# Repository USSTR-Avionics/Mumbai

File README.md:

`aamchi mumbai!!!`

# Introduction

Welcome to our hardware-based repository, dedicated to providing innovative designs for modular boards that utilize the CANbus interface. At our repository, we strive to bring the benefits of modularity to hardware design, allowing for greater flexibility, scalability, and customization. Our designs are built using the robust and reliable CANbus interface, ensuring efficient communication and seamless integration between modules. Whether you're a hardware enthusiast, a researcher, or an engineer looking to build custom hardware solutions, our repository has something to offer. Our goal is to create a community of like-minded individuals who are passionate about hardware design, and we invite you to join us on this exciting journey. Browse our collection of designs, collaborate with others, and let's push the boundaries of what's possible with modular hardware.

PDB and GPS copied over from: https://github.com/USSTR-Avionics/PDB and https://github.com/USSTR-Avionics/gps-board

RF board based on OpenLST: https://github.com/OpenLST/openlst-hw

## Standard and Unified Connector Kit
Pinout  
10x2 connector

|  | 1 | 2 | 3 | 4 | 5 | 6 | 7 | 8 | 9 | 10 |
|---|---|---|---|---|---|---|---|---|---|---|
| **A** | GND | 3V3 |GND | 3V3 | GND | 5V | GND | 5V | GND | Bus voltage | 
| **B** | GND | CAN high | CAN low | GND | GPIO | GPIO | GPIO | GPIO | GPIO  | GPIO  

(left to right, topview)

[hard to flip header](https://www.digikey.ca/en/products/detail/sullins-connector-solutions/SFH11-PBPC-D10-ST-BK/1990090)

## PCB Dimensions Drawing

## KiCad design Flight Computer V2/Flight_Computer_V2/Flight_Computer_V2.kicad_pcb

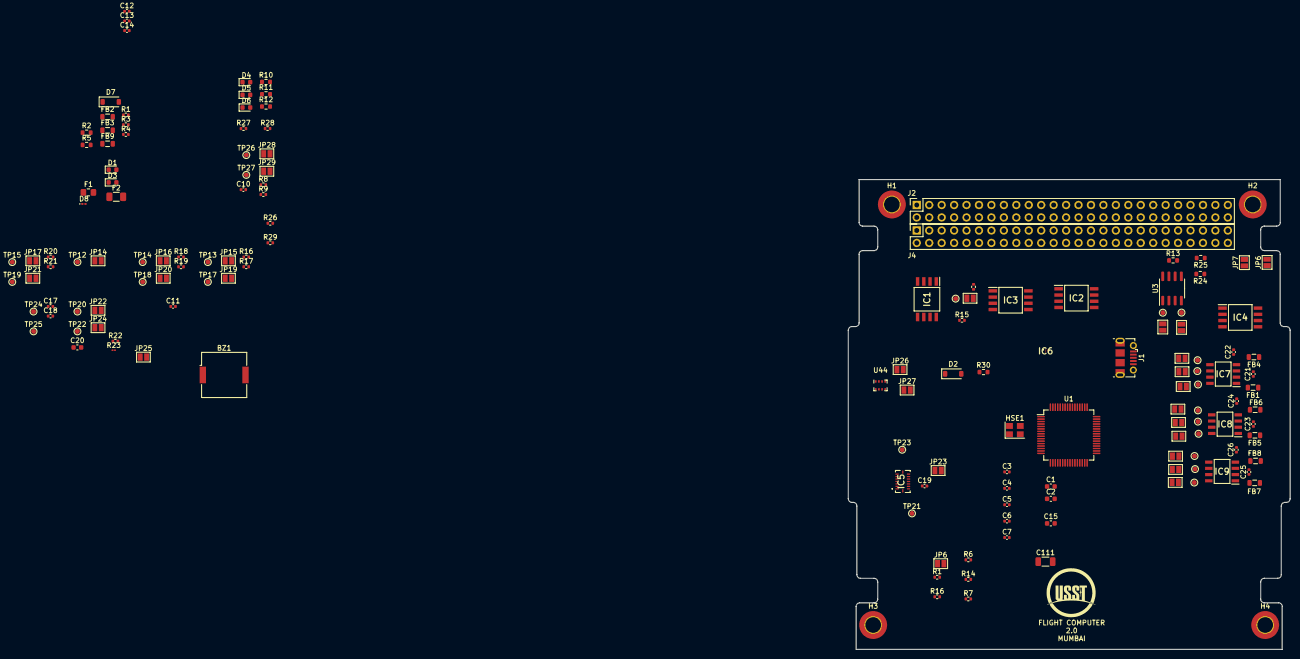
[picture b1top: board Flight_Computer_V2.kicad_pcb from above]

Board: 4 copper layers, 90.2 x 95.9 mm, 154 parts (0 on the bottom side), 82 nets, no tracks yet.

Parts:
BZ1: Active_Buzzer; Buzzer_Murata_PKMCS0909E
C1, C2: 2.2uF; C_0603_1608Metric
C3, C4, C5, C6, C7, C11, C14, C19: 100n; C_0402_1005Metric
C10, C22, C24, C26: 0.1u; C_0402_1005Metric
C12, C13: 10p; C_0402_1005Metric
C15: 10n; C_0603_1608Metric
C17, C18: 100nF; C_0402_1005Metric
C20: 2.2u; C_0603_1608Metric
C21, C23, C25: 1p; C_0402_1005Metric
C111: 4u7; C_1206_3216Metric
D1, D6: RED; LED_0603_1608Metric
D2, D7: B5819W; D_SOD-123
D3: Red; LED_0603_1608Metric
D4: GREEN; LED_0603_1608Metric
D5: YELLOW; LED_0603_1608Metric
D8: RED; LED_0201_0603Metric
F1: 500 mA; Fuse_0805_2012Metric_Pad1.15x1.40mm_HandSolder
F2: 500 mA; Fuse_1206_3216Metric
FB1, FB4, FB5, FB6, FB7, FB8: Ferrite; L_0805_2012Metric
FB2, FB9: 600 @ 600 MHz; L_0805_2012Metric
FB3: 100 @ 100 MHz; L_0805_2012Metric
H1, H2, H3, H4: MountingHole_Pad; MountingHole_3.2mm_M3_ISO7380_Pad_TopBottom
HSE1: 16MHz; Crystal_SMD_3225-4Pin_3.2x2.5mm
IC1, IC2, IC3, IC4: MB85RC256VPF-G-JNERE2; SOIC127P798X210-8N
IC5: BMI088
IC6: MMC5603NJ
IC7, IC8, IC9: MAX31855KASA+T; SOIC127P600X175-8N
J1: USB_B_Micro; USB_Micro-B_Molex-105017-0001
J2, J4: Conn_02x26_Odd_Even; PinSocket_2x26_P2.54mm_Vertical
JP1, JP2, JP3, JP4, JP5, JP6, JP6#2, JP7, JP8, JP9, JP10, JP11, JP12, JP13, JP14, JP15, JP16, JP17, JP18, JP19, JP20, JP21, JP22, JP23, JP24, JP25, JP26, JP27, JP28, JP29: SolderJumper-2_P1.3mm_Open_Pad1.0x1.5mm
R1, R1#2, R6, R7, R14, R14#2, R15, R16, R16#2, R17, R18, R19, R20, R21: 10k; R_0402_1005Metric
R2, R30: 1.5k; R_0603_1608Metric
R3, R4: 1.5k; R_0402_1005Metric
R5: 2.2k; R_0603_1608Metric
R8, R9: 4.7k; R_0402_1005Metric
R10, R11, R12: 500; R_0603_1608Metric
R13: 120; R_0603_1608Metric
R22: 2.7k; R_0402_1005Metric
R23: 2.7k; R_01005_0402Metric
R24, R25: 2k; R_0603_1608Metric
R26, R27, R28, R29: 150; R_0402_1005Metric
TP1, TP2, TP3, TP4, TP5, TP6, TP7, TP8, TP9, TP10, TP11, TP12, TP13, TP14, TP15, TP16, TP17, TP18, TP19, TP20, TP21, TP22, TP23, TP24, TP25, TP26, TP27: TestPoint_Small; TestPoint_Pad_D1.0mm
U1: STM32F405RGTx; LQFP-64_10x10mm_P0.5mm
U3: MCP2562-E-SN; SOIC-8_3.9x4.9mm_P1.27mm
U44: BMP280; Bosch_LGA-8_2x2.5mm_P0.65mm_ClockwisePinNumbering

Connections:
3V3IN: D2.2 (A), J4.27, J4.28
5VIN: D7.2 (A), J2.47, J2.49, J4.25, J4.26
+3.3V: C10.1, C17.1, C18.1, D1.2 (A), FB2.2, JP6.1 (A), R3.1, R4.1, R8.2, R9.2, R24.1, R25.1, U3.5 (Vio), U44.2 (CSB), U44.6 (VDDIO), U44.8 (VDD)
+3.3VA: C14.1, C15.1, FB3.2, U1.13 (VDDA)
+3V3: C3.1, C4.1, C5.1, C6.1, C7.1, C11.1, C19.1, C20.1, C22.1, C24.1, C26.1, C111.1, FB3.1, IC1.8 (VDD), IC2.1 (A0), IC2.8 (VDD), IC3.2 (A1), IC3.8 (VDD), IC4.3 (A2), IC4.8 (VDD), IC5.3 (VDD), IC5.7 (PS), IC5.11 (VDDIO), IC6.B1 (VDD), IC7.4 (VCC), IC8.4 (VCC), IC9.4 (VCC), R6.1, R7.1, R14.1, R14#2.1, R15.1, R16.1, R16#2.1, R17.1, R18.1, R19.1, R20.1, R21.1, R22.1, R23.1, U1.1 (VBAT), U1.19 (VDD), U1.32 (VDD), U1.48 (VDD), U1.64 (VDD)
+5V: D8.2 (A), FB9.2, U3.3 (VDD)
/420_1: R26.2, U1.14 (PA0)
/420_2: R27.2, U1.15 (PA1)
/420_3: R28.2, U1.16 (PA2)
/420_4: R29.2, U1.17 (PA3)
/ACCELROMETER/SCL: J2.43, JP7.1 (A), JP18.2 (B), JP19.2 (B), JP20.2 (B), JP21.2 (B), JP24.2 (B), JP25.2 (B), JP27.2 (B), JP28.2 (B), R3.2, R14#2.2, R16.2, R18.2, R20.2, R25.2, U1.58 (PB6)
/ACCELROMETER/SDA: J2.41, JP6#2.1 (A), JP14.2 (B), JP15.2 (B), JP16.2 (B), JP17.2 (B), JP22.2 (B), JP23.2 (B), JP26.2 (B), JP29.1 (A), R4.2, R24.2, U1.59 (PB7)
/BUZZER: BZ1.1 (-), U1.41 (PA8)
/CAN CONTROLLER/CANH: J2.42, R13.1, U3.7 (CANH)
/CAN CONTROLLER/CANL: J2.44, R13.2, U3.6 (CANL)
/CAN CONTROLLER/CAN_RX: JP5.2 (B), U1.61 (PB8)
/CAN CONTROLLER/CAN_TX: JP4.2 (B), U1.62 (PB9)
/GREEN: R10.1, U1.20 (PA4)
/MICROCONTROLLER/BOOT0: JP6.2 (B), R1.2, R1#2.2, U1.60 (BOOT0)
/MICROCONTROLLER/HSC_IN: C12.1, HSE1.1, U1.5 (PH0)
/MICROCONTROLLER/HSC_OUT: C13.1, HSE1.3, U1.6 (PH1)
/MICROCONTROLLER/PWR_LED_K: D1.1 (K), D8.1 (K), R2.1, R30.1
/MICROCONTROLLER/SPI1_CLK: JP3.2 (B), JP10.2 (B), JP13.2 (B), U1.21 (PA5)
/MICROCONTROLLER/SPI1_MISO: JP1.2 (B), JP8.2 (B), JP11.2 (B), U1.22 (PA6)
/MICROCONTROLLER/USB_D+: J1.3 (D+), U1.45 (PA12)
/MICROCONTROLLER/USB_D-: J1.2 (D-), U1.44 (PA11)
/MICROCONTROLLER/VCAP1: C1.1, U1.31 (VCAP_1)
/MICROCONTROLLER/VCAP2: C2.1, U1.47 (VCAP_2)
/RED: R12.1, U1.27 (PB1)
/TCSS1: JP2.2 (B), U1.8 (PC0)
/TCSS2: JP9.2 (B), U1.9 (PC1)
/TCSS3: JP12.2 (B), U1.10 (PC2)
/WP1: IC1.7 (WP), U1.11 (PC3)
/WP2: IC2.7 (WP), U1.24 (PC4)
/WP3: IC3.7 (WP), U1.25 (PC5)
/WP4: IC4.7 (WP), U1.37 (PC6)
/YELLOW: R11.1, U1.26 (PB0)
GND: BZ1.2 (+), C1.2, C2.2, C10.2, C11.2, C12.2, C13.2, C14.2, C15.2, C17.2, C18.2, C19.2, C20.2, C22.2, C24.2, C26.2, D4.1 (K), D5.1 (K), D6.1 (K), H1.1, H2.1, H3.1, H4.1, HSE1.2, HSE1.4, IC1.4 (VSS), IC2.4 (VSS), IC3.4 (VSS), IC4.4 (VSS), IC5.4 (GNDA), IC5.6 (GNDIO), IC5.10 (SDO2), IC5.15 (SDO1), IC6.A1 (VSA), IC7.1 (GND), IC8.1 (GND), IC9.1 (GND), J1.5 (GND), J4.9, J4.14, J4.17, J4.29, J4.30, J4.32, J4.48, J4.49, R1#2.1, R2.2, R5.2, R26.1, R27.1, R28.1, R29.1, R30.2, U1.12 (VSSA), U1.18 (VSS), U1.63 (VSS), U3.2 (VSS), U3.8 (STBY), U44.1 (GND), U44.5 (SDO), U44.7 (GND)
unnamed: C3.2, C4.2, C5.2, C6.2, C7.2, C111.2
unnamed: D2.1 (K), F1.1
unnamed: D3.2 (A), U1.33 (PB12)
unnamed: D3.1 (K), R5.1
unnamed: D4.2 (A), R10.2
unnamed: D5.2 (A), R11.2
unnamed: D6.2 (A), R12.2
unnamed: D7.1 (K), F2.1
unnamed: F1.2, FB2.1
unnamed: F2.2, FB9.1
unnamed: IC1.6 (SCL), JP18.1 (A), R6.2, TP16.1
unnamed: IC1.5 (SDA), JP14.1 (A), R15.2, TP12.1
unnamed: IC2.6 (SCL), JP19.1 (A), R7.2, TP17.1
unnamed: IC2.5 (SDA), JP15.1 (A), R17.2, TP13.1
unnamed: IC3.6 (SCL), JP20.1 (A), R14.2, TP18.1
unnamed: IC3.5 (SDA), JP16.1 (A), R19.2, TP14.1
unnamed: IC4.6 (SCL), JP21.1 (A), R16#2.2, TP19.1
unnamed: IC4.5 (SDA), JP17.1 (A), R21.2, TP15.1
unnamed: IC5.8 (SCL/SCK), JP25.1 (A), TP23.1
unnamed: IC5.9 (SDA/SDI), JP23.1 (A), TP21.1
unnamed: IC6.A2 (SCL), JP24.1 (A), R22.2, TP22.1
unnamed: IC6.B2 (SDA), JP22.1 (A), R23.2, TP20.1
unnamed: IC7.5 (SCK), JP3.1 (A), TP3.1
unnamed: IC7.7 (SO), JP1.1 (A), TP1.1
unnamed: C21.2, FB4.2, IC7.3 (T+)
unnamed: C21.1, FB1.2, IC7.2 (T-)
unnamed: IC7.6 (~CS), JP2.1 (A), TP2.1
unnamed: IC8.5 (SCK), JP10.1 (A), TP8.1
unnamed: IC8.7 (SO), JP8.1 (A), TP6.1
unnamed: C23.2, FB6.2, IC8.3 (T+)
unnamed: C23.1, FB5.2, IC8.2 (T-)
unnamed: IC8.6 (~CS), JP9.1 (A), TP7.1
unnamed: IC9.5 (SCK), JP13.1 (A), TP11.1
unnamed: IC9.7 (SO), JP11.1 (A), TP9.1
unnamed: C25.2, FB8.2, IC9.3 (T+)
unnamed: C25.1, FB7.2, IC9.2 (T-)
unnamed: IC9.6 (~CS), JP12.1 (A), TP10.1
unnamed: JP4.1 (A), TP4.1, U3.1 (TXD)
unnamed: JP5.1 (A), TP5.1, U3.4 (RXD)
unnamed: JP26.1 (A), TP24.1, U44.3 (SDI)
unnamed: JP27.1 (A), TP25.1, U44.4 (SCK)
unnamed: JP28.1 (A), TP26.1
unnamed: JP29.2 (B), TP27.1
VBUS: J1.1 (VBUS), J4.35, J4.36

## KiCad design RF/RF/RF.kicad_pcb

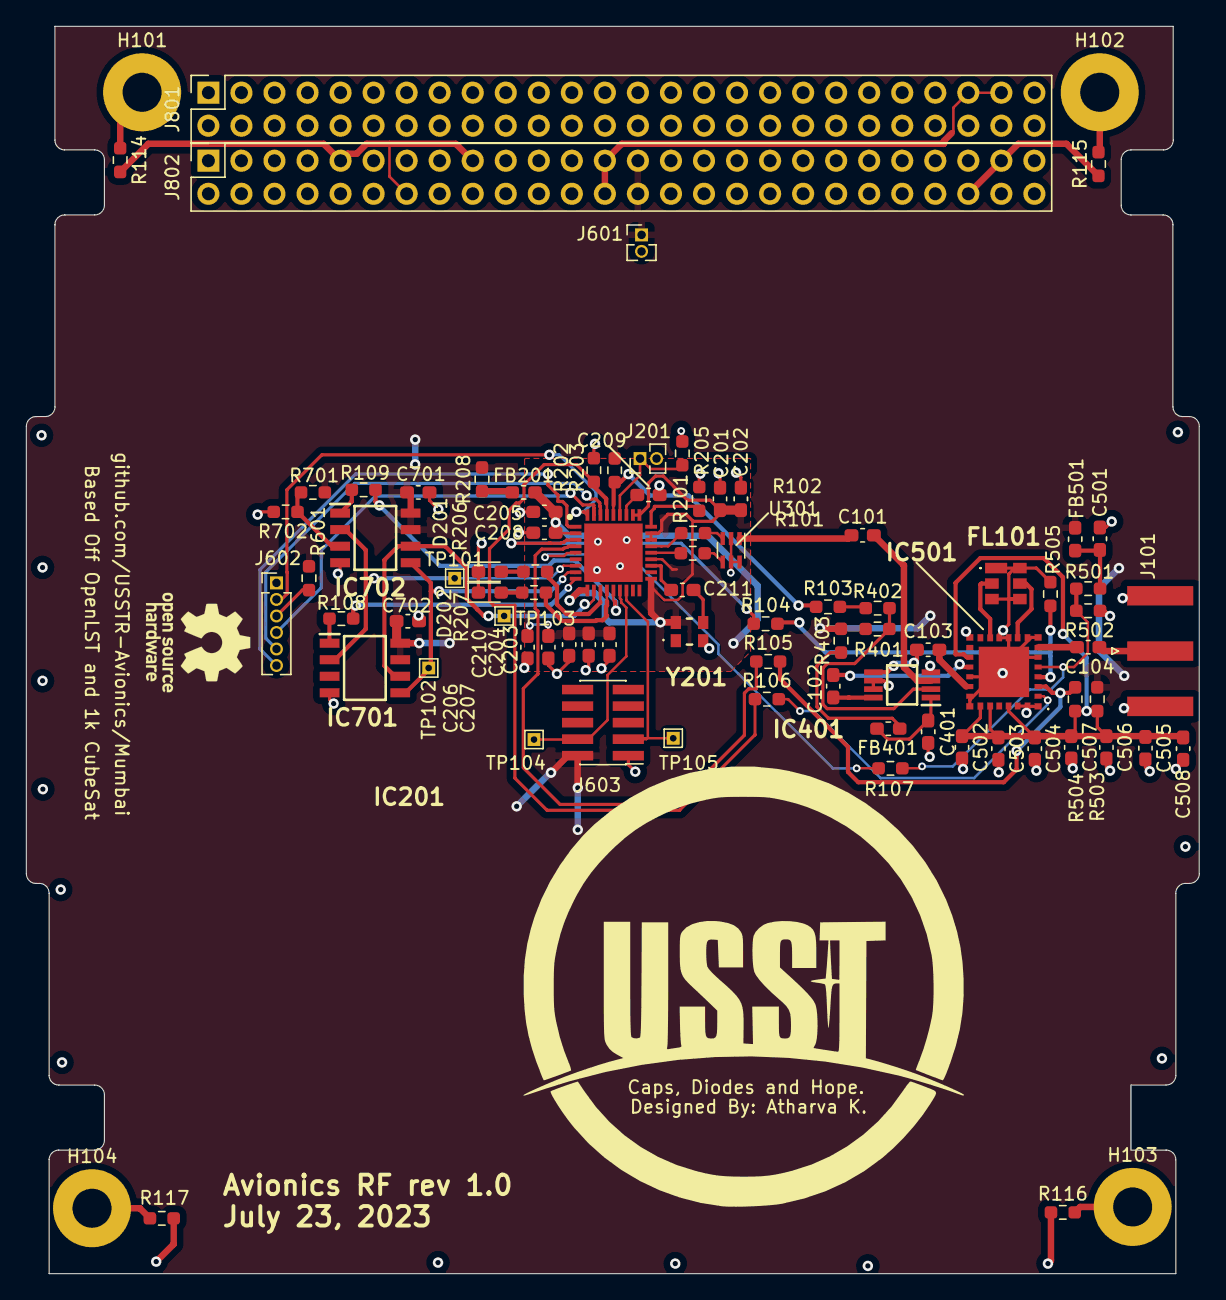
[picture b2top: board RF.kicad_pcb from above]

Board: 4 copper layers, 90.2 x 95.9 mm, 86 parts (0 on the bottom side), 62 nets.

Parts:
C101, C102, C103, C104, C207, C208: 220pF; C_0603_1608Metric_Pad1.08x0.95mm_HandSolder
C201, C202, C209, C507: 1uF; C_0603_1608Metric_Pad1.08x0.95mm_HandSolder
C203, C204, C205, C206, C210, C401, C501, C505, C506, C508, C701, C702: 0.1uF; C_0603_1608Metric_Pad1.08x0.95mm_HandSolder
C211: 0.01uF; C_0603_1608Metric_Pad1.08x0.95mm_HandSolder
C502, C503: 47uF; C_0603_1608Metric_Pad1.08x0.95mm_HandSolder
C504: 4.7uF; C_0603_1608Metric_Pad1.08x0.95mm_HandSolder
D201, D202: LED; LED_0603_1608Metric_Pad1.05x0.95mm_HandSolder
FB201: Z = 1k@ 100MHz; L_0603_1608Metric_Pad1.05x0.95mm_HandSolder
FB401, FB501: Z = 1k @ 100M; L_0603_1608Metric_Pad1.05x0.95mm_HandSolder
FL101: SF2446E
H101, H102, H103, H104: MountingHole_Pad; MountingHole_3mm_Pad
IC201: CC1110F16RHHR; QFN50P600X600X100-37N-D
IC401: PE4250MLI-Z; SOP65P488X107-8N
IC501: RFFM6406SR; RFFM6403
IC701: 23K256-I_SN; SOIC127P600X175-8N
IC702: SST25VF512A-33-4C-SAE; SOIC127P600X175-8N
J101: Conn_Coaxial; SMA_Amphenol_132289_EdgeMount
J201, J601: Conn_01x02; PinHeader_1x02_P1.27mm_Vertical
J602: Conn_01x06; PinHeader_1x06_P1.27mm_Vertical
J603: Conn_02x05_Odd_Even; PinHeader_2x05_P1.27mm_Vertical_SMD
J801, J802: Conn_02x26_Odd_Even; PinSocket_2x26_P2.54mm_Vertical
R101, R102, R103, R104, R105, R106, R107, R108, R109, R208, R402, R403, R503: 0R; R_0603_1608Metric_Pad0.98x0.95mm_HandSolder
R114, R115, R116, R117, R401, R601, R701: DNP; R_0603_1608Metric_Pad0.98x0.95mm_HandSolder
R201: 56k 1%; R_0603_1608Metric_Pad0.98x0.95mm_HandSolder
R202, R203: 10k 1%; R_0603_1608Metric_Pad0.98x0.95mm_HandSolder
R205, R702: 10k; R_0603_1608Metric_Pad0.98x0.95mm_HandSolder
R206, R207, R504, R505: 1k; R_0603_1608Metric_Pad0.98x0.95mm_HandSolder
R501: 3.09k 1%; R_0603_1608Metric_Pad0.98x0.95mm_HandSolder
R502: 6.65k 1%; R_0603_1608Metric_Pad0.98x0.95mm_HandSolder
TP101: MISO; TestPoint_THTPad_1.0x1.0mm_Drill0.5mm
TP102: MOSI; TestPoint_THTPad_1.0x1.0mm_Drill0.5mm
TP103: SCK; TestPoint_THTPad_1.0x1.0mm_Drill0.5mm
TP104: CC_DD; TestPoint_THTPad_1.0x1.0mm_Drill0.5mm
TP105: CC_DC; TestPoint_THTPad_1.0x1.0mm_Drill0.5mm
U301: 0433BM15A0001; Balun_Johanson_0896BM15A0001
Y201: TG2520SMN 27.000M-MCGNNM3; TG2520SMN25000MMCGNNM3

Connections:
+3.3V: C701.1, C702.1, FB501.2, IC701.7 (~HOLD), IC701.8 (VCC), IC702.7 (HOLD#), IC702.8 (VDD), J601.1, J603.2, J802.27, J802.28, R203.1, R208.2, R401.1, R403.2, R503.2, R601.2, R701.1
+3.3VA: C201.1, C202.1, C203.1, C204.1, C205.1, C206.1, C207.1, C208.1, C210.1, FB201.2, IC201.2 (DVDD_1), IC201.10 (DVDD_2), IC201.19 (AVDD_1), IC201.22 (AVDD_2), IC201.25 (AVDD_3), IC201.26 (AVDD_4), IC201.28 (GUARD), IC201.29 (AVDD_DREG), J201.2, Y201.4 (VCC)
+5V: J801.47, J801.49, J802.25, J802.26
/Balun/CC_RF_N: R102.2, U301.3
/Balun/CC_RF_P: R101.2, U301.4
/Balun/UNBALANCED_RF: C101.1, U301.1
/CC1110/AIN0: IC201.5 (P0_0), R107.1
/CC1110/CC_DC: IC201.16 (P2_2), J603.3, TP105.1
/CC1110/CC_DD: IC201.15 (P2_1), J603.4, TP104.1
/CC1110/CC_RF_N: IC201.24 (RF_N), R102.1
/CC1110/CC_RF_P: IC201.23 (RF_P), R101.1
/CC1110/CC_SOC_OC: C211.2, IC201.21 (XOSC_Q1)
/CC1110/LST_TX_MODE: IC201.33 (P1_6), R106.1, R202.1
/CC1110/RF_BYP: IC201.3 (P1_1), R104.1
/CC1110/RF_EN: IC201.4 (P1_0), R105.1
/CC1110/UART0_CTS: IC201.1 (P1_2), J602.6
/CC1110/UART0_RTS: IC201.36 (P1_3), J602.2
/CC1110/UART0_RX: IC201.35 (P1_4), J602.4
/CC1110/UART0_TX: IC201.34 (P1_5), J602.5
/CC1110/~FLASH_CS: IC201.14 (P2_0), R109.1
/CC1110/~LST_RX_MODE: IC201.32 (P1_7), R103.1, R203.2
/CC1110/~SRAM_CS: IC201.9 (P0_4), R108.1
/External Memory/~FLASH_CS: IC702.1 (CE#), R109.2
/External Memory/~SRAM_CS: IC701.1 (~CS), R108.2
/MISO: IC201.7 (P0_2), IC701.2 (SO), IC702.2 (SO), TP101.1
/MOSI: IC201.8 (P0_3), IC701.5 (SI), IC702.5 (SI), TP102.1
/RF Front End/ANTENNA: C104.1, IC501.7 (ANT)
/RF Front End/LST_TX_MODE: IC501.2 (TR), R106.2
/RF Front End/PA_VAPC: IC501.5 (VAPC), R107.2, R501.2, R502.1
/RF Front End/RF_BYP: IC501.4 (BYP), R104.2, R505.2
/RF Front End/RF_EN: IC501.3 (EN), R105.2, R504.1
/RF Front End/RX: C102.2, IC501.18 (RX)
/RF Front End/SAW1: FL101.5 (OUTPUT), IC501.10 (SAW1)
/RF Front End/SAW2: FL101.2 (INPUT), IC501.13 (SAW2)
/RF Front End/TX: C103.2, IC501.20 (TX)
/RF Switch/RX: C102.1, IC401.8 (RF2)
/RF Switch/TX: C103.1, IC401.5 (RF1)
/RF Switch/UNBALANCED_RF: C101.2, IC401.3 (RFC)
/RF Switch/~LST_RX_MODE: R103.2, R402.1
/SCK: IC201.11 (P0_5), IC701.6 (SCK), IC702.6 (SCK), TP103.1
GND: C201.2, C202.2, C203.2, C204.2, C205.2, C206.2, C207.2, C208.2, C209.2, C210.2, C401.2, C501.2, C502.2, C503.2, C504.2, C505.2, C506.2, C507.2, C508.2, C701.2, C702.2, D201.1 (K), D202.1 (K), FL101.1 (GND_1), FL101.3 (GND_2), FL101.4 (GND_3), FL101.6 (GND_4), IC201.37 (AGND), IC401.4 (N/C_OR_GND), IC401.6 (GND_1), IC401.7 (GND_2), IC501.1 (GND_1), IC501.6 (GND_2), IC501.8 (GND_3), IC501.9 (GND_4), IC501.11 (GND_5), IC501.12 (GND_6), IC501.15 (GND_7), IC501.19 (GND_8), IC501.21 (GND_9), IC501.22 (GND_10), IC501.27 (GND_11), IC501.28 (GND_12), IC501.29 (EP), IC701.4 (VSS), IC702.4 (VSS), J101.2 (Ext), J601.2, J602.1, J603.1, J802.9, J802.14, J802.17, J802.29, J802.30, J802.32, J802.48, J802.49, R114.1, R115.1, R116.1, R117.1, R201.2, R202.2, R205.2, R502.2, R505.1, R702.2, U301.2 (GND), U301.5 (GND), U301.6 (GND), Y201.2 (GND)
unnamed: C501.1, FB501.1, R501.1
unnamed: D201.2 (A), R206.2
unnamed: D202.2 (A), R207.2
unnamed: FB201.1, R208.1
unnamed: FB401.1, R403.1
unnamed: H101.1, R114.2
unnamed: H102.1, R115.2
unnamed: H103.1, R116.2
unnamed: H104.1, R117.2
unnamed: C209.1, IC201.30 (DCOUPL)
unnamed: IC201.12 (P0_6), R206.1
unnamed: IC201.13 (P0_7), R207.1
unnamed: IC201.27 (RBIAS), R201.1
unnamed: IC201.31 (RESET_N), J201.1, R205.1
unnamed: IC401.2 (V1), R401.2, R402.2
unnamed: C401.1, FB401.2, IC401.1 (V2)
unnamed: C502.1, C503.1, C504.1, C505.1, C506.1, C507.1, C508.1, IC501.17 (VCC_RX), IC501.23 (VDD), IC501.24 (VCC_TX1), IC501.26 (VCC_TX2), R503.1, R504.2
unnamed: IC702.3 (WP#), R701.2, R702.1
unnamed: C104.2, J101.1 (In)
unnamed: J602.3, R601.1
unnamed: C211.1, Y201.3 (OUT)

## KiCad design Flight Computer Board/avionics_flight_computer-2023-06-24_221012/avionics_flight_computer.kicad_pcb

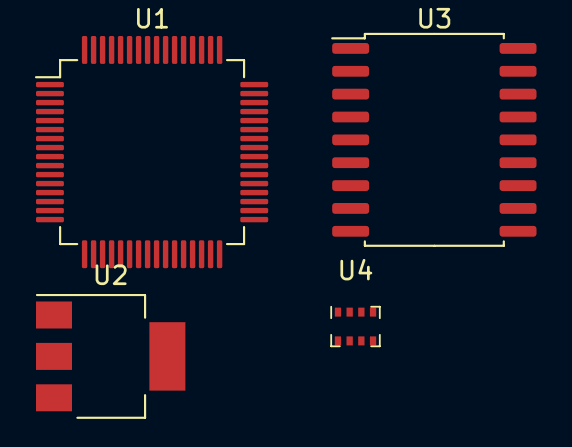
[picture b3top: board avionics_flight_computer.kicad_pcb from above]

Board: 2 copper layers, 4 parts (0 on the bottom side), 2 nets, no tracks yet.

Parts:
U1: STM32F405RGTx; LQFP-64_10x10mm_P0.5mm
U2: AMS1117-3.3; SOT-223-3_TabPin2
U3: MCP2515-xSO; SOIC-18W_7.5x11.6mm_P1.27mm
U4: BMP280; Bosch_LGA-8_2x2.5mm_P0.65mm_ClockwisePinNumbering

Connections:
3.3V: U1.1 (VBAT), U1.19 (VDD), U1.32 (VDD), U1.48 (VDD), U1.64 (VDD), U2.2 (VO), U4.2 (CSB), U4.6 (VDDIO), U4.8 (VDD)
GND: U1.12 (VSSA), U1.18 (VSS), U1.63 (VSS), U2.1 (GND), U3.9 (VSS), U4.1 (GND), U4.5 (SDO), U4.7 (GND)

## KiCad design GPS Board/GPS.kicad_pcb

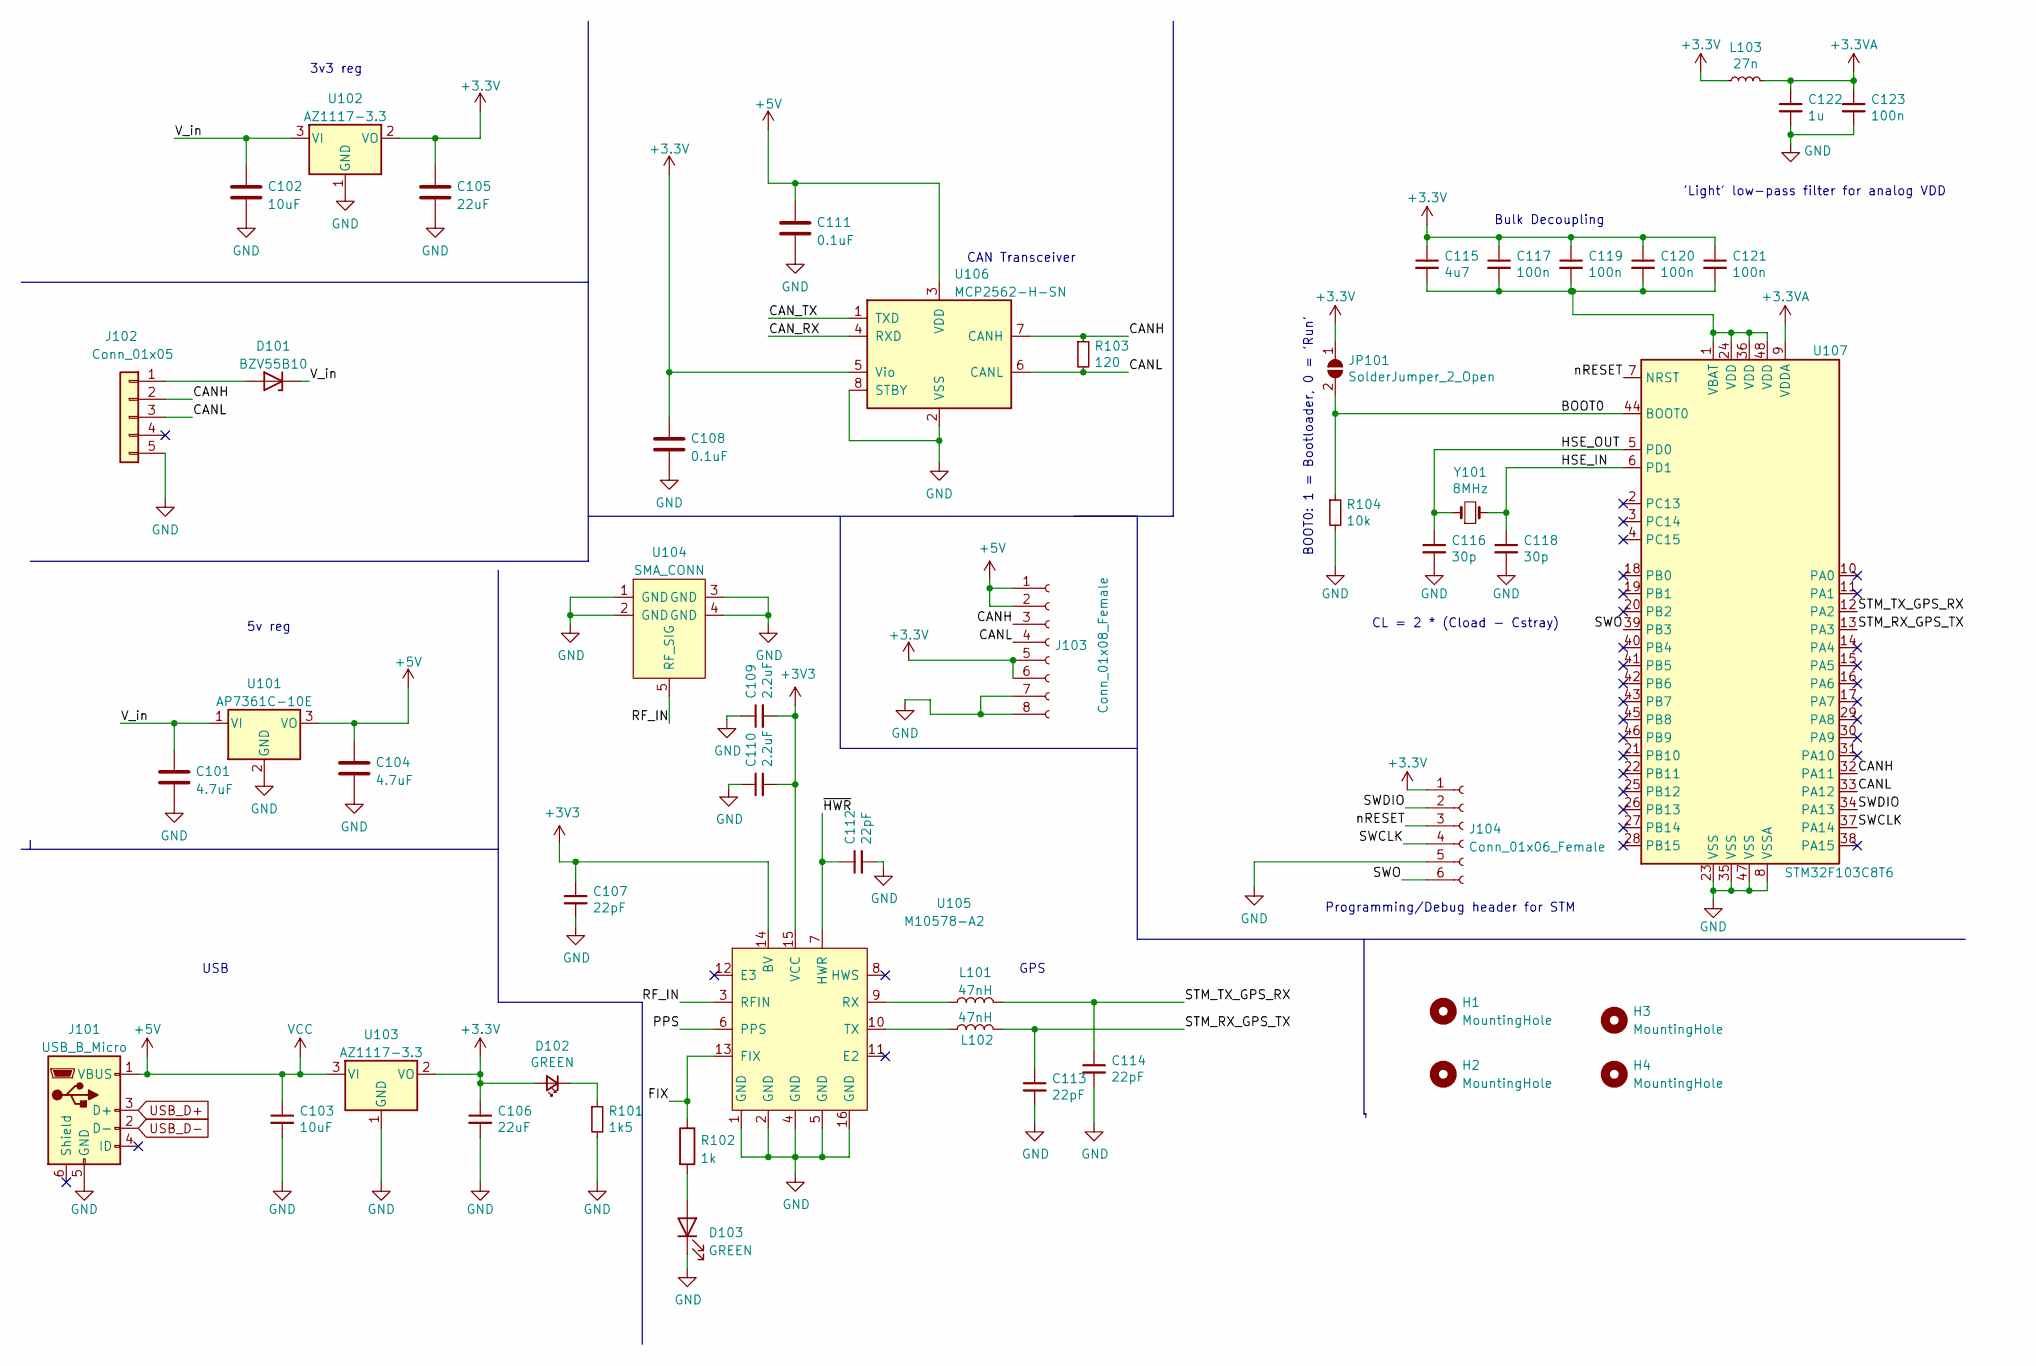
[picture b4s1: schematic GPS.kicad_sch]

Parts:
C101, C104: 4.7uF; C_0805_2012Metric
C102: 10uF; C_0805_2012Metric
C103: 10uF; C_0603_1608Metric; LCSC Part # C15849
C105: 22uF; C_0805_2012Metric
C106: 22uF; C_0805_2012Metric; LCSC Part # C15849
C107, C112, C113, C114: 22pF; C_0805_2012Metric; LCSC Part # C15849
C108, C111: 0.1uF; C_0805_2012Metric
C109, C110: 2.2uF; C_0805_2012Metric; LCSC Part # C15849
C115: 4u7; C_0805_2012Metric_Pad1.18x1.45mm_HandSolder; LCSC Part # C19666
C116, C118: 30p; C_0805_2012Metric_Pad1.18x1.45mm_HandSolder; LCSC Part # C1570
C117, C119, C120, C121, C123: 100n; C_0805_2012Metric_Pad1.18x1.45mm_HandSolder; LCSC Part # C1525
C122: 1u; C_0805_2012Metric_Pad1.18x1.45mm_HandSolder; LCSC Part # C52923
D101: BZV55B10; D_MiniMELF
D102: GREEN; LED_0805_2012Metric_Pad1.15x1.40mm_HandSolder; LCSC Part # C72043
D103: GREEN; LED_0805_2012Metric_Pad1.15x1.40mm_HandSolder
H1, H2, H3, H4: MountingHole; MountingHole_3.2mm_M3
J101: USB_B_Micro; USB_Micro-B_Wuerth_629105150521
J102: Conn_01x05; PinHeader_1x05_P1.27mm_Horizontal
J103: Conn_01x08_Female; PinHeader_1x08_P1.27mm_Horizontal
J104: Conn_01x06_Female; Tag-Connect_TC2030-IDC-FP_2x03_P1.27mm_Vertical
JP101: SolderJumper_2_Open; SolderJumper-2_P1.3mm_Open_Pad1.0x1.5mm
L101, L102: 47nH; L_0805_2012Metric_Pad1.15x1.40mm_HandSolder
L103: 27n; L_0402_1005Metric; LCSC Part # C18830
R101: 1k5; R_0805_2012Metric; LCSC Part # C22843
R102: 1k; R_0805_2012Metric_Pad1.20x1.40mm_HandSolder
R103: 120; R_0805_2012Metric; LCSC Part # C25744
R104: 10k; R_0805_2012Metric_Pad1.20x1.40mm_HandSolder; LCSC Part # C25744
U101: AP7361C-10E; SOT-223-3_TabPin2
U102, U103: AZ1117-3.3; SOT-223
U104: SMA_CONN; connector_SMA_3-1478978-1
U105: M10578-A2
U106: MCP2562-H-SN; SOIC-8_3.9x4.9mm_P1.27mm
U107: STM32F103C8T6; LQFP-48_7x7mm_P0.5mm; LCSC Part # C8734
Y101: 8MHz; Crystal_SMD_5032-2Pin_5.0x3.2mm; LCSC Part # C115962

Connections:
+3.3V: C105.1, C106.1, C108.1, C115.1, C117.1, C119.1, C120.1, C121.1, D102.2 (A), J103.5, J103.6, J104.1, JP101.1 (A), L103.1, U102.2 (VO), U103.2 (VO), U106.5 (Vio)
+3.3VA: C122.1, C123.1, L103.2, U107.9 (VDDA)
+3V3: C107.1, C109.2, C110.2, U105.14 (BV), U105.15 (VCC)
+5V: C103.1, C104.1, C111.1, J101.1 (VBUS), J103.1, J103.2, U101.3 (VO), U103.3 (VI), U106.3 (VDD)
/BOOT0: JP101.2 (B), R104.1, U107.44 (BOOT0)
/CANH: J102.2, J103.3, R103.1, U106.7 (CANH), U107.32 (PA11)
/CANL: J102.3, J103.4, R103.2, U106.6 (CANL), U107.33 (PA12)
/CAN_RX: U106.4 (RXD)
/CAN_TX: U106.1 (TXD)
/FIX: R102.1, U105.13 (FIX)
/HSE_IN: C118.1, U107.6 (PD1), Y101.2
/HSE_OUT: C116.1, U107.5 (PD0), Y101.1
/PPS: U105.6 (PPS)
/RF_IN: U104.5 (RF_SIG), U105.3 (RFIN)
/STM_RX_GPS_TX: C113.1, L102.2, U107.13 (PA3)
/STM_TX_GPS_RX: C114.1, L101.2, U107.12 (PA2)
/SWCLK: J104.4, U107.37 (PA14)
/SWDIO: J104.2, U107.34 (PA13)
/SWO: J104.6, U107.39 (PB3)
/V_in: C101.1, C102.1, D101.1 (K), U101.1 (VI), U102.3 (VI)
/nRESET: J104.3, U107.7 (NRST)
/~HWR: C112.1, U105.7 (HWR)
GND: C101.2, C102.2, C103.2, C104.2, C105.2, C106.2, C107.2, C108.2, C109.1, C110.1, C111.2, C112.2, C113.2, C114.2, C116.2, C118.2, C122.2, C123.2, D103.1 (K), J101.5 (GND), J102.5, J103.7, J103.8, J104.5, R101.2, R104.2, U101.2 (GND), U102.1 (GND), U103.1 (GND), U104.1 (GND), U104.2 (GND), U104.3 (GND), U104.4 (GND), U105.1 (GND), U105.2 (GND), U105.4 (GND), U105.5 (GND), U105.16 (GND), U106.2 (VSS), U106.8 (STBY), U107.8 (VSSA), U107.23 (VSS), U107.35 (VSS), U107.47 (VSS)
unnamed: C115.2, C117.2, C119.2, C120.2, C121.2, U107.1 (VBAT), U107.24 (VDD), U107.36 (VDD), U107.48 (VDD)
unnamed: D101.2 (A), J102.1
unnamed: D102.1 (K), R101.1
unnamed: D103.2 (A), R102.2
unnamed: L101.1, U105.9 (RX)
unnamed: L102.1, U105.10 (TX)

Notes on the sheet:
USB
CAN Transceiver
'Light' low-pass filter for analog VDD
5v reg
Bulk Decoupling
CL = 2 * (Cload - Cstray)
Programming/Debug header for STM
GPS
3v3 reg
BOOT0: 1 = Bootloader, 0 = 'Run'

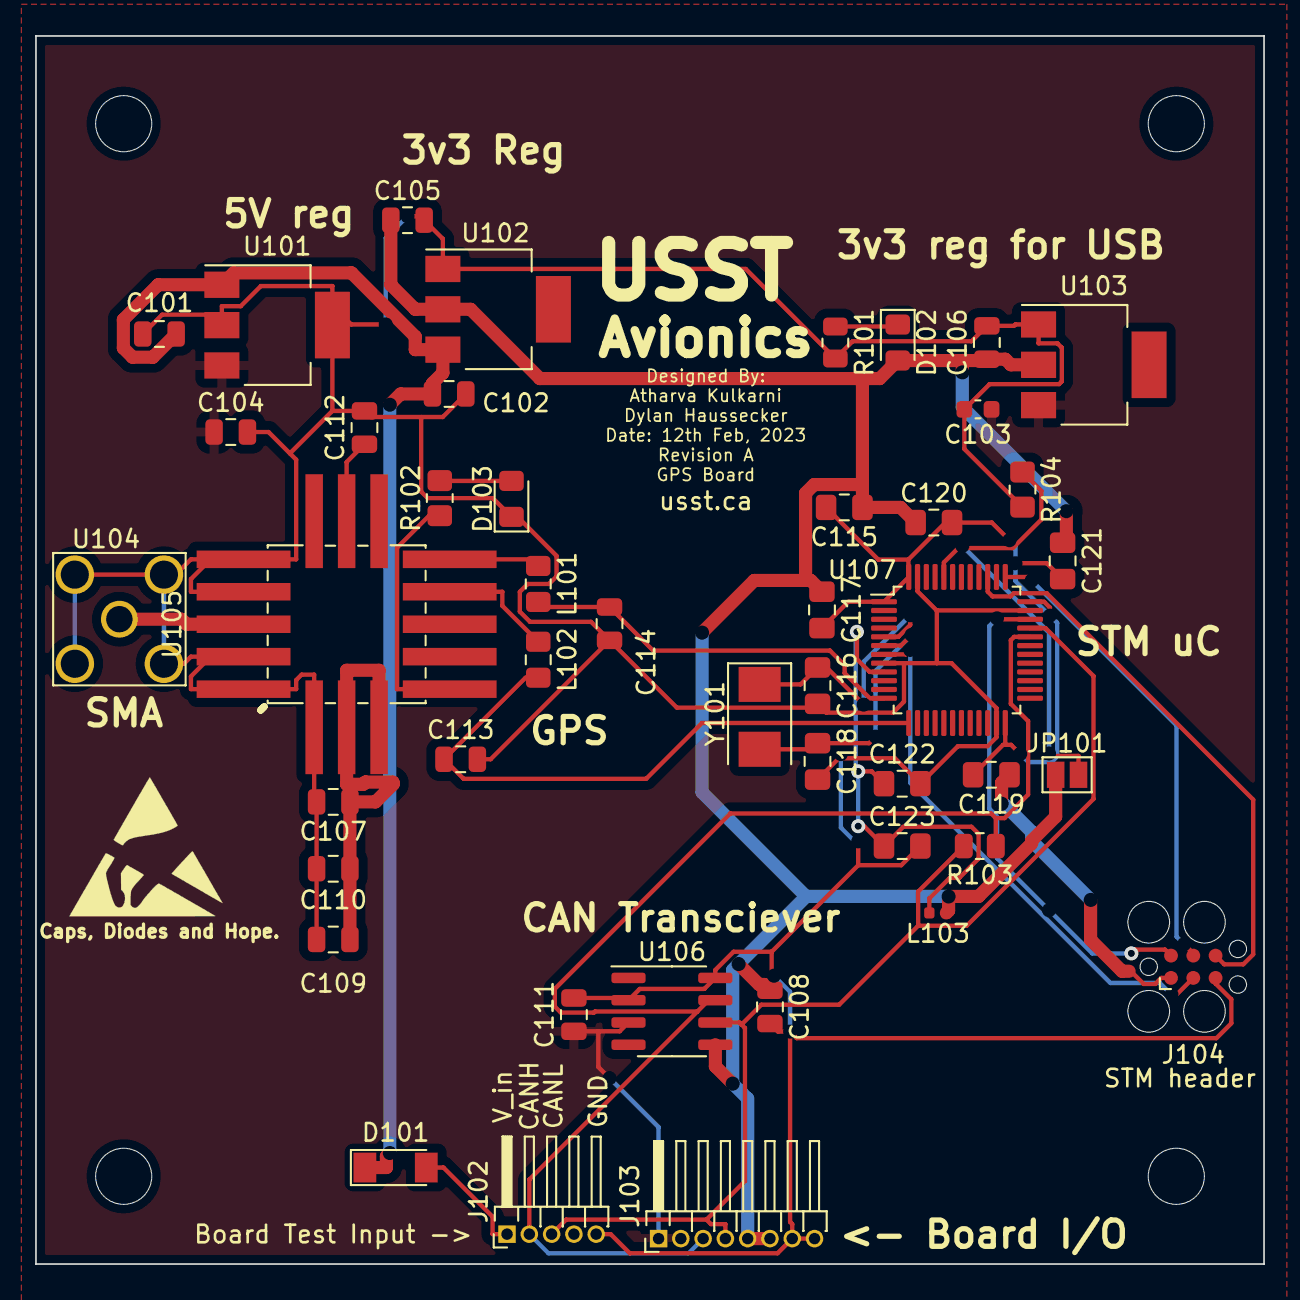
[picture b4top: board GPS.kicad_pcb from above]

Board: 2 copper layers, 70.0 x 70.0 mm, 49 parts (0 on the bottom side), 26 nets.

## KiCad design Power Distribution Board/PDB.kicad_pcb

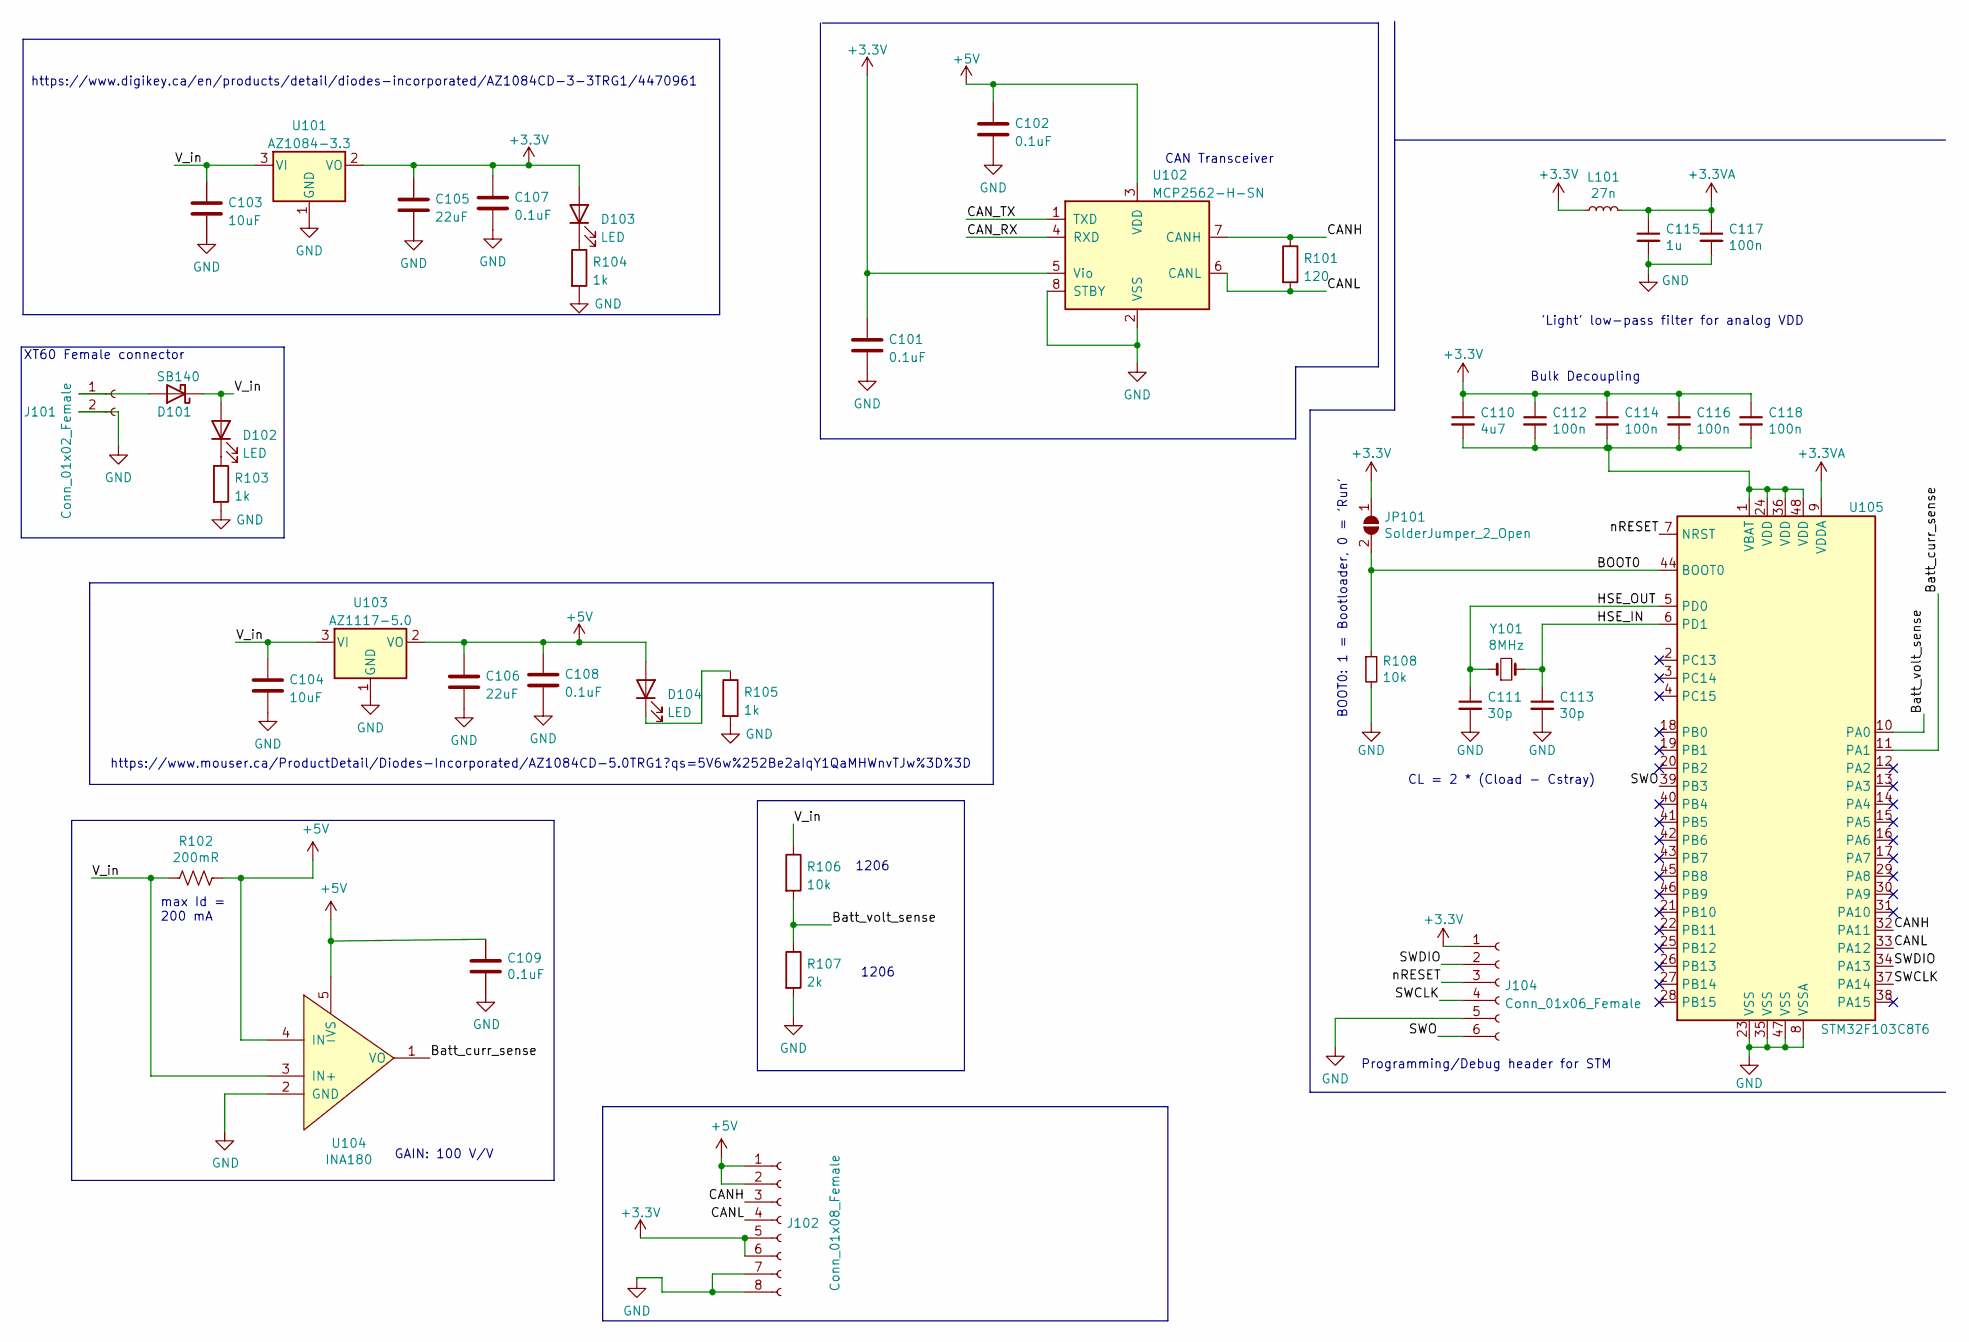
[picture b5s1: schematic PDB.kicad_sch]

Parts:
C101, C102, C107, C108, C109: 0.1uF; C_0805_2012Metric_Pad1.18x1.45mm_HandSolder
C103, C104: 10uF; C_0805_2012Metric_Pad1.18x1.45mm_HandSolder
C105, C106: 22uF; C_0805_2012Metric_Pad1.18x1.45mm_HandSolder
C110: 4u7; C_0805_2012Metric_Pad1.18x1.45mm_HandSolder; LCSC Part # C19666
C111, C113: 30p; C_0805_2012Metric_Pad1.18x1.45mm_HandSolder; LCSC Part # C1570
C112, C114, C116, C117, C118: 100n; C_0805_2012Metric_Pad1.18x1.45mm_HandSolder; LCSC Part # C1525
C115: 1u; C_0805_2012Metric_Pad1.18x1.45mm_HandSolder; LCSC Part # C52923
D101: SB140; D_DO-41_SOD81_P10.16mm_Horizontal
D102, D103, D104: LED; LED_0805_2012Metric_Pad1.15x1.40mm_HandSolder
J101: Conn_01x02_Female; AMASS_XT60PW-F_1x02_P7.20mm_Horizontal
J102: Conn_01x08_Female; PinHeader_1x08_P1.27mm_Horizontal
J104: Conn_01x06_Female; Tag-Connect_TC2030-IDC-FP_2x03_P1.27mm_Vertical
JP101: SolderJumper_2_Open; SolderJumper-2_P1.3mm_Open_Pad1.0x1.5mm
L101: 27n; L_0402_1005Metric; LCSC Part # C18830
R101: 120; R_0805_2012Metric_Pad1.20x1.40mm_HandSolder
R102: 200mR; R_0805_2012Metric_Pad1.20x1.40mm_HandSolder
R103, R104, R105: 1k; R_0805_2012Metric_Pad1.20x1.40mm_HandSolder
R106: 10k; R_1206_3216Metric_Pad1.30x1.75mm_HandSolder
R107: 2k; R_1206_3216Metric_Pad1.30x1.75mm_HandSolder
R108: 10k; R_0805_2012Metric_Pad1.20x1.40mm_HandSolder; LCSC Part # C25744
U101: AZ1084-3.3; TO-252-2
U102: MCP2562-H-SN; SOIC-8_3.9x4.9mm_P1.27mm
U103: AZ1117-5.0; TO-252-3_TabPin2
U104: INA180; SOT-23-5_HandSoldering
U105: STM32F103C8T6; LQFP-48_7x7mm_P0.5mm; LCSC Part # C8734
Y101: 8MHz; Crystal_SMD_5032-2Pin_5.0x3.2mm; LCSC Part # C115962

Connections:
+3.3V: C101.1, C105.1, C107.1, C110.1, C112.1, C114.1, C116.1, C118.1, D103.2 (A), J102.5, J102.6, J104.1, JP101.1 (A), L101.1, U101.2 (VO), U102.5 (Vio)
+3.3VA: C115.1, C117.1, L101.2, U105.9 (VDDA)
+5V: C102.1, C106.1, C108.1, C109.1, D104.2 (A), J102.1, J102.2, R102.1, U102.3 (VDD), U103.2 (VO), U104.4 (IN-), U104.5 (VS)
/BOOT0: JP101.2 (B), R108.1, U105.44 (BOOT0)
/Batt_curr_sense: U104.1 (VO), U105.11 (PA1)
/Batt_volt_sense: R106.2, R107.1, U105.10 (PA0)
/CANH: J102.3, R101.1, U102.7 (CANH), U105.32 (PA11)
/CANL: J102.4, R101.2, U102.6 (CANL), U105.33 (PA12)
/CAN_RX: U102.4 (RXD)
/CAN_TX: U102.1 (TXD)
/HSE_IN: C113.1, U105.6 (PD1), Y101.2
/HSE_OUT: C111.1, U105.5 (PD0), Y101.1
/SWCLK: J104.4, U105.37 (PA14)
/SWDIO: J104.2, U105.34 (PA13)
/SWO: J104.6, U105.39 (PB3)
/V_in: C103.1, C104.1, D101.1 (K), D102.2 (A), R102.2, R106.1, U101.3 (VI), U103.3 (VI), U104.3 (IN+)
/nRESET: J104.3, U105.7 (NRST)
GND: C101.2, C102.2, C103.2, C104.2, C105.2, C106.2, C107.2, C108.2, C109.2, C111.2, C113.2, C115.2, C117.2, J101.2, J102.7, J102.8, J104.5, R103.2, R104.2, R105.2, R107.2, R108.2, U101.1 (GND), U102.2 (VSS), U102.8 (STBY), U103.1 (GND), U104.2 (GND), U105.8 (VSSA), U105.23 (VSS), U105.35 (VSS), U105.47 (VSS)
unnamed: C110.2, C112.2, C114.2, C116.2, C118.2, U105.1 (VBAT), U105.24 (VDD), U105.36 (VDD), U105.48 (VDD)
unnamed: D101.2 (A), J101.1
unnamed: D102.1 (K), R103.1
unnamed: D103.1 (K), R104.1
unnamed: D104.1 (K), R105.1

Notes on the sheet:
BOOT0: 1 = Bootloader, 0 = 'Run'
https://www.mouser.ca/ProductDetail/Diodes-Incorporated/AZ1084CD-5.0TRG1?qs=5V6w%252Be2aIqY1QaMHWnvTJw%3D%3D
CL = 2 * (Cload - Cstray)
'Light' low-pass filter for analog VDD
Bulk Decoupling
https://www.digikey.ca/en/products/detail/diodes-incorporated/AZ1084CD-3-3TRG1/4470961
GAIN: 100 V/V
max Id = 200 mA
XT60 Female connector
CAN Transceiver
Programming/Debug header for STM
1206
